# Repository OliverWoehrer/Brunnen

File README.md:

# Brunnen IoT - Pumpensteuerung mit Internetanbindung
**Dislaimer:** This is a hobby project planed, built, programmed and tested by me. All design choices are based on the individual and unique use case of my groundwater well in my garden in Vienna. 
## Introduction
### Idea
The idea was to build a remote control unit and meassurement unit in my groundwater well in my garden for the automatic irrigation system installed.
### Concept
It was necessary to control the electrical water pump of the automatic irrigation system and monitor the water flow in order to ensure the proper functioning of the hardware. Therefore the water flow out of the well, the water pressure inside the system and the water level of the well are being constantly meassured. In addition to that the power supply of the electrical water pump is switched on/off according to the user-defined intervals. The water pump is running as soon as it is connected to 230 VAC.<br/>
Due to the fact that only on weekends somebody is there, the hole device has internet access and sends an daily e-mail with the meassurement data of the that day. The heart of the project is the ESP32 micro controller which supports multiple I/Os as well as a WiFi module.
### Sketch

## User Manual
### Operating the Device
#### Physical Button
The device itself is located inside the well and has only one physical button. The button has two functions: short press and long press.
- Short Press: Tells the the device to connect to the wifi and toggles the web server. The push needs to be at least 100 ms long. This prevents a unintended button push when working inside the well.
- Long Press: Toggles the relais and therefore the connected water pump. Has to be pushed three seconds or longer as a safty meassure to ensure that the relais only gets toggled on purpose. 
#### User Interface Web Server
This is the main user interface and is a simple HTTP web server consisting of two pages:
- Homepage (index.html): Displays the current time and sensor values meassured by the device. This allows for real time screening and refreshes automatically every second to poll the newest data.
- Interval (interval.html): This sub-page allows to check and set the intervals of the water pump. This means when to switch on/off the relais.
### LEDs and their meaning
The PCB hold four (colored) status LEDs and one small red power supply LED indicating the microcontroller has power.
- **Blue LED:** Is the cycle LED which is turned on during the meassurement cycle. This leads to a blinking behaviour once a second.
- **Red LED:** Indicates an error, the log file should be read for further information.
- **Yellow LED:** Warning purpose, lights up when the relais and therefore the connected water pump is active
- **Green LED:** Indicates that the user interface web server is up and running

## Hardware and Schematics
### Sensors
There are three main physical values that are messured: The water flow in the exit pipe of the well, the water pressure inside the pipe and the water pressure at the bottom of the well.
- **Water Level Sensor TL231:** The sensor is a two wire analog sensor with a voltage supply of 24 VDC and and current flow between 4...20 mA. The water level sensor is placed at the bottom of the well and uses the pressure of the surrounding water to conclude the current flow trough the wires. Because this sensor has a relatively high energy consumption of up to 0.5 W it was a requirement to make the power supply switchable. To read the current flow of the sensor into the microcontroller a 160 Ohm resistor is connected in series in the GND connected wire of the sensor. This makes for a voltage of 640...3200 mV.</br>
Because of this resistor the 24 VDC sensor 
- **Water Flow Sensor YF-B10:**
- **Water Pressure Sensor:**
out of the well to check weather the irrigation system actually uses water,  
### Relais
### SD Card Shield
### Power Supply
The device is powered over 230 VAC and is plugged in. Because of multiple parts, controllers and sensors there are different voltage levels required across the device (230VAC, 24 VDC, 5 VDC and 3.3 VDC). These levels are achieved through two AC-DC converters from 230 VAC to 24 VDC and 5 VDC respectively. The ESP32 needs 3.3 VDC. The 24 VDC from the water pressure sensor are used for the relais coil as well since it is the highest DC voltage level available on the PCB.</br>
The onboard LDO of the ESP32 development board helps to convert 3.3 VDC from the onboard 5Vext wire. Because it is also possible to power the ESP32 development board over the USB cable connection (which is used when debugging and flashing the controller) there is the possibility that two potential power sources are connected at the same time to the ESP32: The 5 VDC comming from the AC-DC-converter over the 5Vext pin and the 5 VDC comming from the USB cable. The ESP32 development board has an onboard 5N5819 Shottky diode from USB to the 5Vext wire to protect the USB driver from high voltages. To also protect the 5 VDC converter as the other potential power source the same Shottky diode is used in simmilar fashion. The 5N5819 is chossen deliberate to reduce any differences between the two protecting diodes such as different temperature behaviours, etc.
### Sketch

### Layout
### Connections
To protect the device from colder temperatures during the winter, it is recommended to remove the device from the well during this time. In order to help with reconnecting the cables and sensors properly the cables are labled with color as followed.

|  Connection  |   Port [color]  |  Pin [color]  |
| ------------- | -------------| ------------- |
|  Water Flow Sensor (signal)  |  Port 1 [black]  |  1 [white]  |
|  Water Flow Sensor (+5V)  | Port 1 [black] | 2 [green] |
|  Water Flow Sensor (GND)  | Port 1 [black] | 3 [brown] |
|  Button  |  Port 2  |  1 [red]  |
|  Button  | Port 2 | 2 [green] |
|  Water Level Sensor (GND)  |  Port 3 [blue] | 1 [brown] |
|  Water Level Sensor (+24V)  | Port 3 [blue] | 2 [green] |
|  Water Pressure Sensor (signal)  | Port 4 [yellow] | 1 [green] |
|  Water Pressure Sensor (GND)  |  Port 4 [yellow] | 2 [brown] |
|  Water Pressure Sensor (+5V)  |  Port 4 [yellow] | 3 [white] |
|  Power Supply 230AC (L) |  Port 5  |  1 [brown]  |
|  Power Supply 230AC (N)  |  Port 5  |  2 [blue]  |
|  Switched 230VAC (N)  |  Port 5  |  1 [blue]  |
|  Switched 230VAC (L)  |  Port 5  |  2 [brown]  |

## Software
### Flashing Software
The easier way is to use the popular [Arduino IDE](https://www.arduino.cc/en/software) with the easy-to-install ESP32 extension available on the Arduino eco system. Just add the additional board manager as shown in this [Tutorial](https://randomnerdtutorials.com/installing-the-esp32-board-in-arduino-ide-windows-instructions/). After a sucessful installation, download the code in this repository and simply connect to the controller via micro USB. Finally click the upload icon in the IDE. When the four colored LEDs on the PCB start to light up after each other the device booted properly.

### Main Code (code.ino)
### Hardware (hw)
### Data and Time (dt)
### User Interface (ui)

## Data Results
## Lessons Learned

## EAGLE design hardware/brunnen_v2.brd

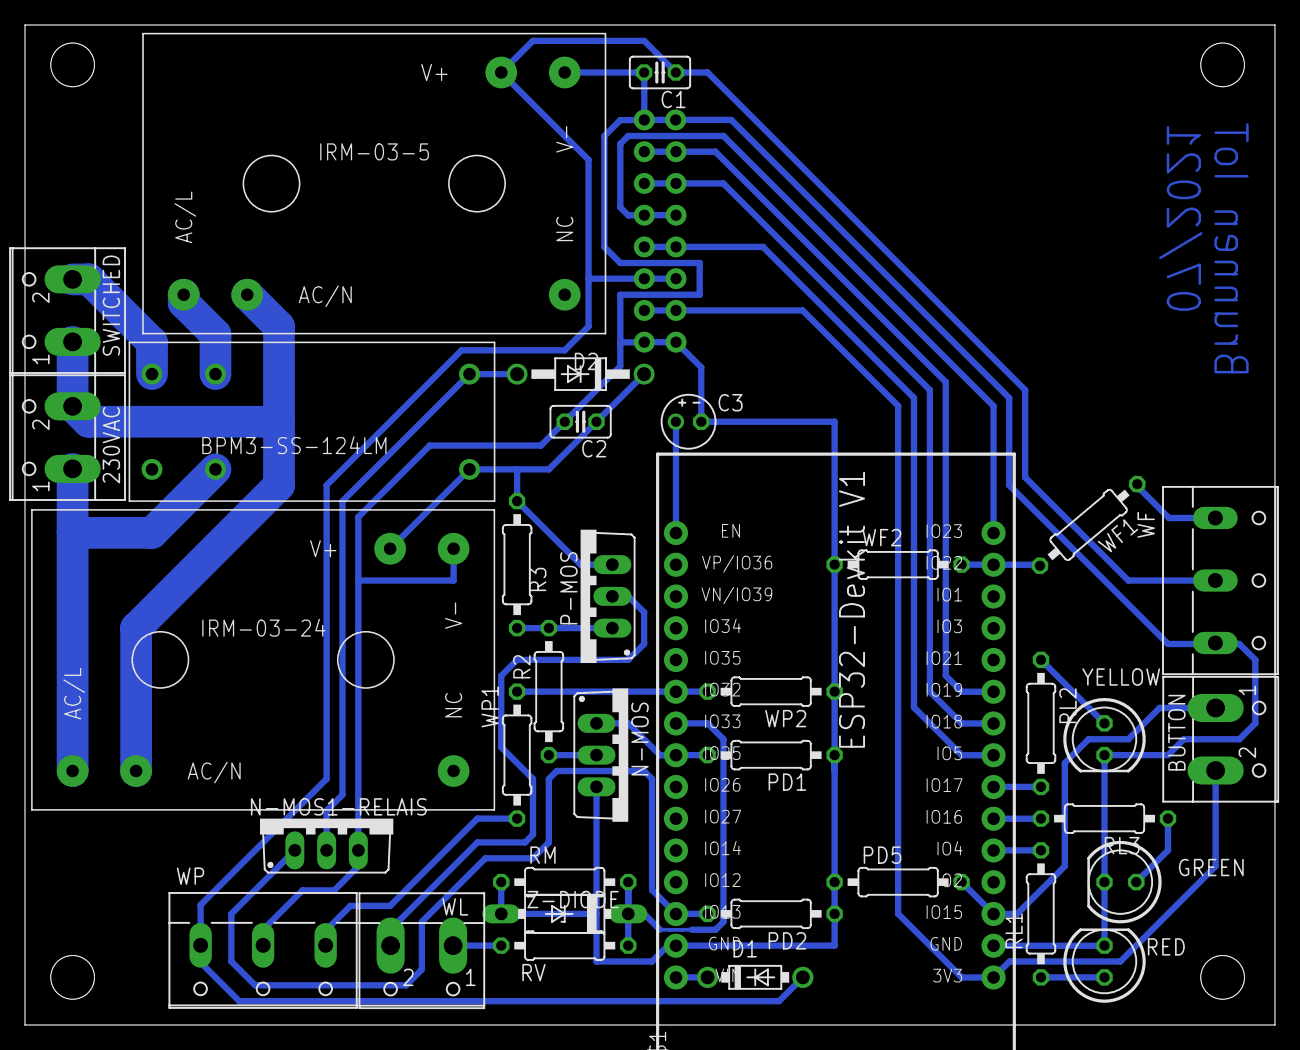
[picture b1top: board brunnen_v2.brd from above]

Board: 2 copper layers, 100.0 x 80.0 mm, 37 parts (1 on the bottom side), 32 nets.

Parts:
230VAC: W237-102
BUTTON: W237-102
C1, C2: 220nF; C025-025X050
C3: 10uF; E2-4
D1: 1N5819; DO41-7.6
D2: 1N4004; DO41-10
GREEN: LED5MM
IRM-03-5: 5VDC; IRM_03
IRM-03-24: 24VDC; IRM_03
N-MOS, N-MOS1-RELAIS: IRFZ24NPBF; TO220BV
P-MOS: IRF9510PBF; TO220BV
PD1, PD2, PD5: 100k; 0207/10
R2: 10k; 0207/10
R3: 2k; 0207/10
RED: LED5MM
RL1, RL2, RL3: 130R; 0207/10
RM: 160R; 0207/10
RV: 130R; 0207/10
SD: 322-16-DUAL
SWITCHED: W237-102
U$1: ESP32DEVKITV1; ESP32-DEVKITV1
U$2: BPM3-SS-124LM
WF: Waterflow; W237-103
WF1: 47k; 0207/10
WF2: 100k; 0207/10
WL: Waterlevel; W237-102
WP: Waterpressure; W237-103
WP1: 5k6; 0207/10
WP2: 10k; 0207/10
YELLOW: LED5MM
Z-DIODE: 3.6V; F126Z10

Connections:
+3V3: BUTTON.2, SD.13, SD.14, U$1.3V3
+5V: C1.1, D1.A, IRM-03-5.V+, SD.11, SD.12, WF.2, WP.3
+24V: C2.1, D2.C, IRM-03-24.V+, P-MOS.S, R3.2, U$2.VDD
AGND: 230VAC.2, IRM-03-5.AC/N, IRM-03-24.AC/N, SWITCHED.1
BTN: BUTTON.1, PD5.2, U$1.D15
GND: C1.2, C2.2, C3.-, GREEN.K, IRM-03-5.V-, IRM-03-24.V-, N-MOS.S, N-MOS1-RELAIS.S, PD1.1, PD2.1, PD5.1, RED.K, RM.1, SD.1, SD.2, SD.15, SD.16, U$1.GND@1, U$1.GND@2, WF.3, WF2.1, WP.2, WP2.1, YELLOW.K, Z-DIODE.A
IN: RM.2, RV.1, U$1.D33, Z-DIODE.C
unnamed: N-MOS.G, PD1.2, U$1.D25
unnamed: N-MOS.D, R2.1
unnamed: P-MOS.G, R2.2, R3.1
unnamed: P-MOS.D, WL.2
unnamed: D1.C, U$1.VIN
unnamed: SWITCHED.2, U$2.P21, U$2.P22
unnamed: WF.1, WF1.1
unnamed: D2.A, N-MOS1-RELAIS.D, U$2.VSS
unnamed: WP.1, WP1.2
unnamed: U$1.D32, WP1.1, WP2.2
unnamed: RV.2, WL.1
unnamed: RED.A, RL1.1
unnamed: RL2.2, U$1.D17
unnamed: RL2.1, YELLOW.A
unnamed: GREEN.A, RL3.1
unnamed: RL3.2, U$1.D16
unnamed: RL1.2, U$1.D4
unnamed: SD.7, SD.8, U$1.D23
unnamed: C3.+, U$1.EN
unnamed: SD.5, SD.6, U$1.D18
unnamed: SD.9, SD.10, U$1.D5
unnamed: SD.3, SD.4, U$1.D19
RELAIS: N-MOS1-RELAIS.G, PD2.2, U$1.D13
V+: 230VAC.1, IRM-03-5.AC/L, IRM-03-24.AC/L, U$2.P11, U$2.P12
WF: U$1.D22, WF1.2, WF2.2

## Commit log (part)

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2021-09-16 public commit, SW version 2
2021-09-16 added ignore file
2021-09-17 fix for week-day-feature
2021-10-05 added script page to plot data files
2021-10-18 changed file structure
2021-10-18 removed additional folders
2022-09-29 restructured hardware module
2022-10-04 restructured data&time module
2022-10-29 added OTA
2022-11-24 added support for OpenMeteo API
2022-11-25 op mode must be set manually for when calling toggle()
2022-11-25 remove serial debug statement
2022-12-15 added CR to newline characters for serial print
2022-12-15 checkboxs now pre-selected
2022-12-18 added error message to smtp session
2022-12-18 added button to clear job list
2022-12-21 disable serial output of OpenWeather response
2022-12-22 added functionality to clear error led and set threshold rain level
2022-12-22 moved functionality to index homepage
2022-12-22 added live upload status
2022-12-22 improved functionality
2022-12-22 introduced heap watcher to manage heap-heavy tasks
2022-12-22 changed functionality: request weather once per day, send mail every other hour
2022-12-22 fix copy&paste error
2023-01-09 changed return value of getWeatherData()
2023-01-09 restructured wifi login to support backup networks
2023-03-03 seperated implementation of hardware and onboard modules
2023-03-18 removed obsolete comments
2023-03-18 merged methods for sensor sampling
2023-03-18 added meangful comments for faster changes
2023-03-18 changed order of module initalization
2023-03-23 merged esp32 schematics into on file
2023-03-25 added config option for larger flash memory partition
2023-03-27 changed time initalization behavior
2023-04-03 fixed typo
2023-04-07 added option to store password in flash
2023-04-07 implemented change of account settings in UI
2023-05-04 updated doc files
2023-05-04 implemented password support at runtime
2023-05-06 changed mail recipient
2023-05-06 Revert "removed faulty return statement from sendMailTask"
    This reverts commit 899987f3ecbea785784dbc2304b22229e771466b.
2023-06-25 changed order of networks to connect to
2023-07-09 added responsive scaling
2023-07-09 reduced connection attempt time out
2023-07-09 added support update OTA for file images
2023-07-25 changed lable to litre per second
2023-09-05 added error handling on faulty lines in data file
2024-08-27 added documentation as PDFs
2024-08-27 removed obsolete log messages
2024-08-27 added comments for better readability
2024-08-27 simple prototype
2024-08-31 renamed main file
2024-08-31 adapted config handler
2024-08-31 added hierachial blueprint (routes) structure
2024-08-31 implemented basic stylings and logs
2024-09-01 restructured routes and template files
2024-09-03 updated config with influx data
2024-09-03 basic database client
2024-09-03 start up script for influx server
2024-09-04 upload logs measurements to database
2024-09-04 fixed bug: use nanoseconds as precision for upload and write
2024-09-04 added measurment query
2024-09-04 removed empty lines
2024-09-04 updated logo
2024-09-04 added comment for alternative layout use
2024-09-05 implemented handler for measurements
2024-09-05 fixed wrong timestamp type
2024-09-10 implemented handler for logs and settings
2024-09-10 moved initalization of app to app.py module
2024-09-10 implemented default error page
2024-09-10 changed default behaviour: return unhandled errors
2024-09-10 render error page for unknown error
2024-09-10 fixed docstring
2024-09-10 fixed empty tables on query and changed behaviour of settings query
2024-09-10 implemented api route
2024-09-11 renamed measurements to data
2024-09-11 implemented data exchange for brunnen
2024-09-11 updated name of gloabl constant
2024-09-11 fixed return of DELETE and GET method
2024-09-13 added default settings
2024-09-13 keep timestamps with timezone
2024-09-13 changed structure of thresholds
2024-09-14 updated settings interface to work with json and not Dataframes
2024-09-14 reformated json names to match with actual key names in code
2024-09-15 implemented support for user credentials
2024-09-15 restructured api blueprints
2024-09-15 implemented login feature
2024-09-15 return only settings updated after the given time (=only greater timestamp), not greater and equals timestamps
2024-09-16 added support for dark user theme
2024-09-16 implemented support to store device access tokens in database
2024-09-16 implemented profile page
2024-09-16 removed left and right padding from main container
2024-09-17 always query dataframe for multiple entries for consistency in query methods
2024-09-17 app blueprint (main blueprint) only for login and logout
2024-09-17 wrote some doc comments, rendering of error messages only for web pages (not entire app)
2024-09-17 global helper functions
2024-09-17 logs get filled on load
2024-09-17 implemented user management with tabs
2024-09-19 added daytime to config
2024-09-19 rewrote update of sync mode to make it more readable
2024-09-19 removed session lifetime
2024-09-19 implemented authentication for device api endpoints
2024-09-19 small changes in color theme of tables and nav bar
2024-09-20 return data in columns not rows
2024-09-20 implemented data plot
2024-09-24 ignore startup scripts
2024-09-24 added global functions to script
2024-09-24 changed tabs style and improved functionality
2024-09-24 implemented new buttons, links and submits
2024-09-24 removed global base template, seperarat templates for page types
2024-09-24 added sub page for logs
2024-09-24 removed unwanted linebreak
2024-09-24 added error handler to global app blueprint
2024-09-24 read app key from environment instead of hardcoded app key
2024-09-24 parse int to prevent issues with integer as text later on
2024-09-24 added limit of 2000 points per query
2024-09-25 added edge case of small aggregation window
2024-09-25 added global scripts to base templates
2024-09-25 include scripts in based template instead
2024-09-25 run init on window load
2024-09-26 renamed to fit actual return type
2024-09-26 fixed aggregation window size by rounding slightly up
2024-09-26 workaround for block and inline-block elements
2024-09-26 implemented live feature
2024-10-03 choose more suitable default values for thresholds
2024-10-03 default styles for h4 and table header color responsive
2024-10-03 implemented interval, synchronization and thresholds endpoints
2024-10-03 removed custom style of google icon font
2024-10-03 responsive landscape mode for chart
2024-10-03 removed import of legacy files
2024-10-03 implementation of settings page
2024-10-04 changed return of empty data instead of raising an error
2024-10-04 refactoring of request structure, use fetch instead if jQuery
2024-10-09 renamed folder
2024-10-09 new structure of repo (moved edge related code into sub-folder)
2024-10-09 return all settings on GET request
2024-12-01 added check for environment variables
2024-12-01 ignore IDE files
2024-12-01 use InfluxDB library for data upload
2024-12-01 building access to backend
2024-12-01 increased partitio for instruction memory
2024-12-04 implementation of service modules (sensors, time and files)
2024-12-04 added lib directory to build process
2024-12-08 fix string assignment: copy bytes into buffer
2024-12-08 removed empty line
2024-12-18 removed old files
2024-12-18 added semaphore for mutex
2024-12-18 refactoring
2024-12-18 remove set method for digital pins
2024-12-18 made globally available initalization on import
2024-12-18 first implementation
2024-12-28 added functionality to change api credentials
2024-12-28 return intervals with seconds
2024-12-28 fixed mutex semaphores with proper clean up strategy
2024-12-28 use strings and not raw bytes to store credentials
2024-12-28 use doc reference inside class directly
2024-12-28 dont mopunt FS in constructor, parse and export logs from file
2024-12-28 print additional information about already connected address
2024-12-28 use newer version of ArduinoJSON
2025-01-01 set timezone for incoming timestamps
2025-01-01 enable authentication for web api
2025-01-01 smaller header size on small screens
2025-01-01 use ChartJS library for visualization
2025-01-01 fixed broken copy function
2025-01-01 parse input parameter to set logging level
2025-01-01 manually built requirements
2025-01-01 fixed broken store function
2025-01-01 use size to check for empty data or logs
2025-01-01 print debug messages always (not matter the number of exported lines)
2025-01-01 use remote connection
2025-01-05 fixed broken sampling
2025-01-05 added function to count lines in data file
2025-01-05 removed led as a visualization of ongoing sensor sampling
2025-01-05 fixed return type of size()
2025-01-05 remove old TODO comments
2025-01-06 query latest timestamp of logs too
2025-01-06 dont throw error on empty data
2025-01-06 log and exit early on mutex fail
2025-01-07 removed fixed time unit, use automatic units instead
2025-01-07 updated more meaningful error message
2025-01-07 removed table pivot (not needed since timestamp query changed)
2025-01-18 added headings
2025-01-18 added support for dynamic host changes
2025-01-18 support for changing host address and port via UI
2025-01-18 fixed log message
2025-01-18 print timestamp if available also to serial
2025-01-18 clear error led after successful sync
2025-03-07 added backtrace to logging file on failure
2025-03-30 implemented layer of cache to reduce file operations
2025-03-30 define batch size globally
2025-03-30 file check now try to open exisiting file to see if they really work
2025-03-30 implement auto fix for broken file
2025-03-30 updated debug messages to match terminology of cached data points
2025-03-30 fix dark mode for data plot
2025-04-15 filter rows with faulty timestamp
2025-04-21 display latest sync timestamp
2025-04-21 remove control characters from log messages
2025-04-21 use local cache copy to reduce critical section
2025-04-21 reoved legacy comment
2025-04-21 use bigger SPIFFS partition
2025-04-25 refactored to use new file manager class
2025-04-25 added comment about return value
2025-05-01 make gauge font size responsive, add option to append new data to plots
2025-05-01 change order or cards on mobile
2025-05-01 remove heading for sup pages
2025-05-27 add disconnect at initalization
2025-05-27 remove email credentials, changed behavior on SD card fail
2025-05-27 changed behavior on full cach
2025-05-27 changed range of date on initialization
2025-05-27 sort logs by date
2025-05-27 removed automatic loading of logs
2025-05-27 changed version to string for OTA updates based on their timestamp
2025-05-27 added proper ogs on execption
2025-06-01 remove redundant heading
2025-06-01 add form for upload of firmware
2025-06-01 add endpoint for edge device to download firmware file
2025-06-01 implemented handling of firmware files
2025-06-01 removed legacy request handlers
2025-06-01 implemented firmware update OTA web
2025-06-01 fixed syntax error in formated strings
2025-06-03 added manifest of PWA installation
2025-06-03 remove support to update settings from the edge
2025-06-10 updated pre-selection to custom so it is compatible with initPicker function
2025-06-10 added function description and improved log messages
2025-06-17 fixed broken URL format
2025-06-17 ignore logs
2025-07-25 added reboot after multiple failed synchs
2025-07-25 implemented runtime wrapper for critical semaphore section
2025-09-05 implemented variable measurement period intervals
2025-09-12 make daytime limits visible in UI
2025-09-12 update daytime limits
2025-09-12 provide docker compose for local database
2025-09-12 fixed wrong return value
2025-09-12 updated sync mode enum to match with system state
2025-09-12 implementation of system state, wrapper for mutex values
2025-09-12 docker compose for system setup
2026-04-21 renamed app to backend
2026-05-10 added sensor data to status message
2026-05-12 basic ui setup
2026-05-15 made log message verbose to prevent spamming by measurement task
2026-05-15 renamed folder docu to readme
2026-05-15 moved readme file
2026-05-15 added custom web components to compiler exception
2026-05-17 renamed global style sheet
2026-05-17 added date and time picker components
